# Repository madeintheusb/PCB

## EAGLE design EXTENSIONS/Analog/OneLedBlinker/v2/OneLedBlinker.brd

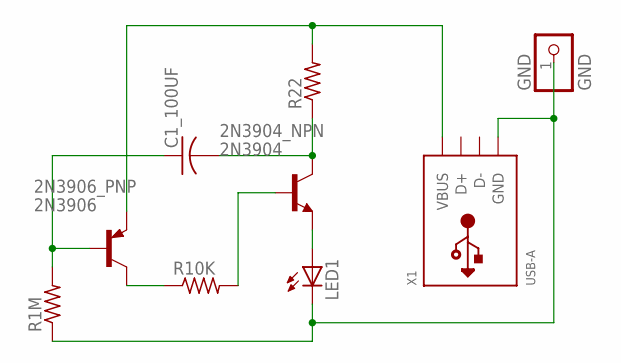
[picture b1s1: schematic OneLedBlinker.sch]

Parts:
2N3904_NPN: 2N3904; TO92
2N3906_PNP: 2N3906; TO92
C1_100UF: C-US025-030X050; C025-030X050
GND: GND; 1X01
LED1: LED5MM
R1M, R10K, R22: R-US_0207/10; 0207/10
X1: USB-A; MOLEX_480371000

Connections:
unnamed: 2N3906_PNP.3 (E), R22.2, X1.1 (VBUS)
unnamed: 2N3904_NPN.1 (C), C1_100UF.2, R22.1
unnamed: 2N3904_NPN.3 (E), LED1.A
unnamed: GND.1, LED1.K (C), R1M.1, X1.4 (GND)
unnamed: 2N3906_PNP.2 (B), C1_100UF.1, R1M.2
unnamed: 2N3906_PNP.1 (C), R10K.1
unnamed: 2N3904_NPN.2 (B), R10K.2

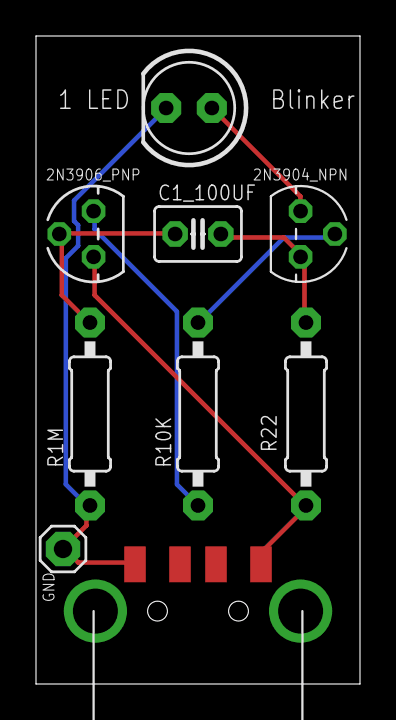
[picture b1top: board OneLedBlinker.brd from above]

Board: 2 copper layers, 18.0 x 36.0 mm, 9 parts (0 on the bottom side), 7 nets.

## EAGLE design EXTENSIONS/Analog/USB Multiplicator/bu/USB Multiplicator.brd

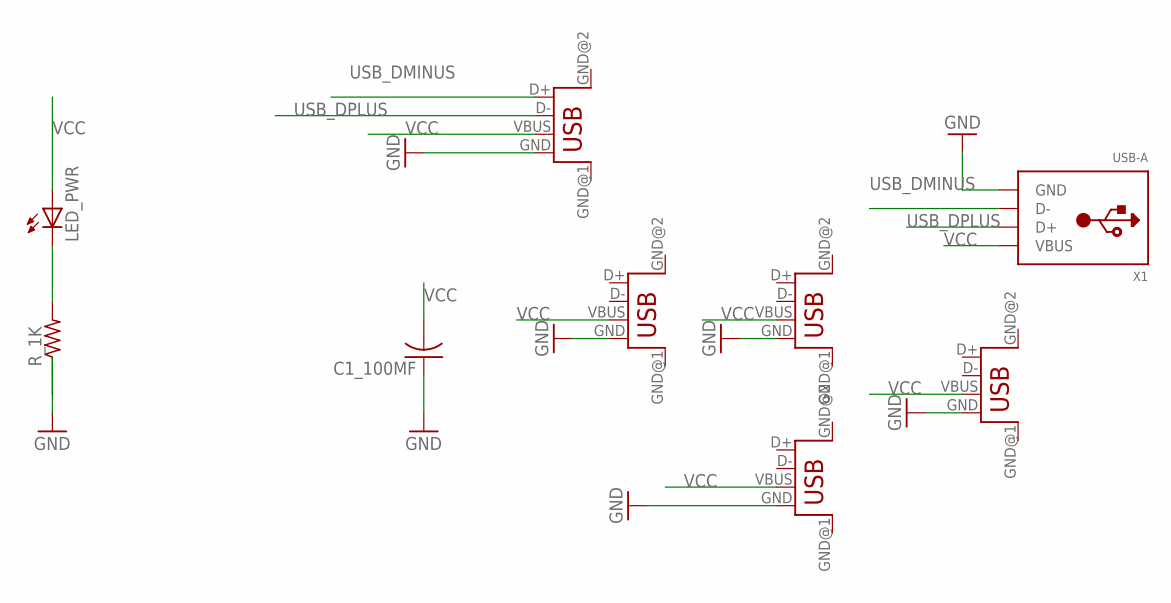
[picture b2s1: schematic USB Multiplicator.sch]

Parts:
C1_100MF: C-US025-030X050; C025-030X050
LED_PWR: LEDSMT1206; 1206
R_1K: R-US_R1206; R1206
USB_OUT_2, USB_OUT_3, USB_OUT_4, USB_OUT_5: USB; USB-FEMALE-A-PTH
USB_OUT_WITH_DATA_1: USB; USB-FEMALE-A-PTH
X1: USB-A; MOLEX_480371000

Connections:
GND: C1_100MF.1, R_1K.1, USB_OUT_2.GND, USB_OUT_3.GND, USB_OUT_4.GND, USB_OUT_5.GND, USB_OUT_WITH_DATA_1.GND, X1.4 (GND); also elsewhere on the board
unnamed: LED_PWR.C, R_1K.2
USB_DMINUS: USB_OUT_WITH_DATA_1.D+, X1.2 (D-)
USB_DPLUS: USB_OUT_WITH_DATA_1.D-, X1.3 (D+)
VCC: C1_100MF.2, LED_PWR.A, USB_OUT_2.VBUS, USB_OUT_3.VBUS, USB_OUT_4.VBUS, USB_OUT_5.VBUS, USB_OUT_WITH_DATA_1.VBUS, X1.1 (VBUS); also elsewhere on the board

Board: 2 copper layers, 10 parts (0 on the bottom side), 5 nets, no tracks yet.

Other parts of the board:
USB_OUT_6: USB; USB-FEMALE-A-PTH

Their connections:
GND: USB_OUT_6.GND; also elsewhere on the board
VCC: USB_OUT_6.VBUS; also elsewhere on the board

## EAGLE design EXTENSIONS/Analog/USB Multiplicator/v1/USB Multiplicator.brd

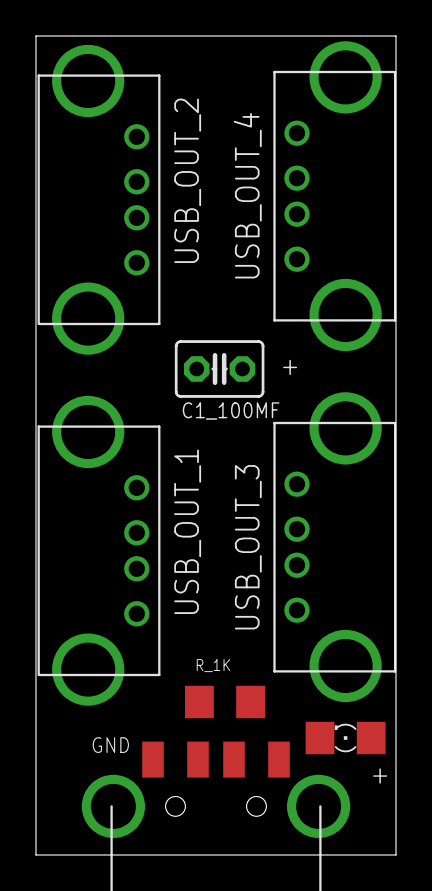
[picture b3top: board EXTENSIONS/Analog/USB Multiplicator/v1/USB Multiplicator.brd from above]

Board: 2 copper layers, 20.0 x 45.5 mm, 8 parts (0 on the bottom side), 5 nets, no tracks yet.

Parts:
C1_100MF: C025-030X050
LED_PWR: 1206
R_1K: R1206
USB_OUT_1, USB_OUT_2, USB_OUT_3, USB_OUT_4: USB; USB-FEMALE-A-PTH
X1: USB-A; MOLEX_480371000

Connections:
GND: C1_100MF.1, R_1K.1, USB_OUT_1.GND, USB_OUT_2.GND, USB_OUT_3.GND, USB_OUT_4.GND, X1.4
unnamed: LED_PWR.C, R_1K.2
USB_DMINUS: USB_OUT_1.D+, X1.2
USB_DPLUS: USB_OUT_1.D-, X1.3
VCC: C1_100MF.2, LED_PWR.A, USB_OUT_1.VBUS, USB_OUT_2.VBUS, USB_OUT_3.VBUS, USB_OUT_4.VBUS, X1.1

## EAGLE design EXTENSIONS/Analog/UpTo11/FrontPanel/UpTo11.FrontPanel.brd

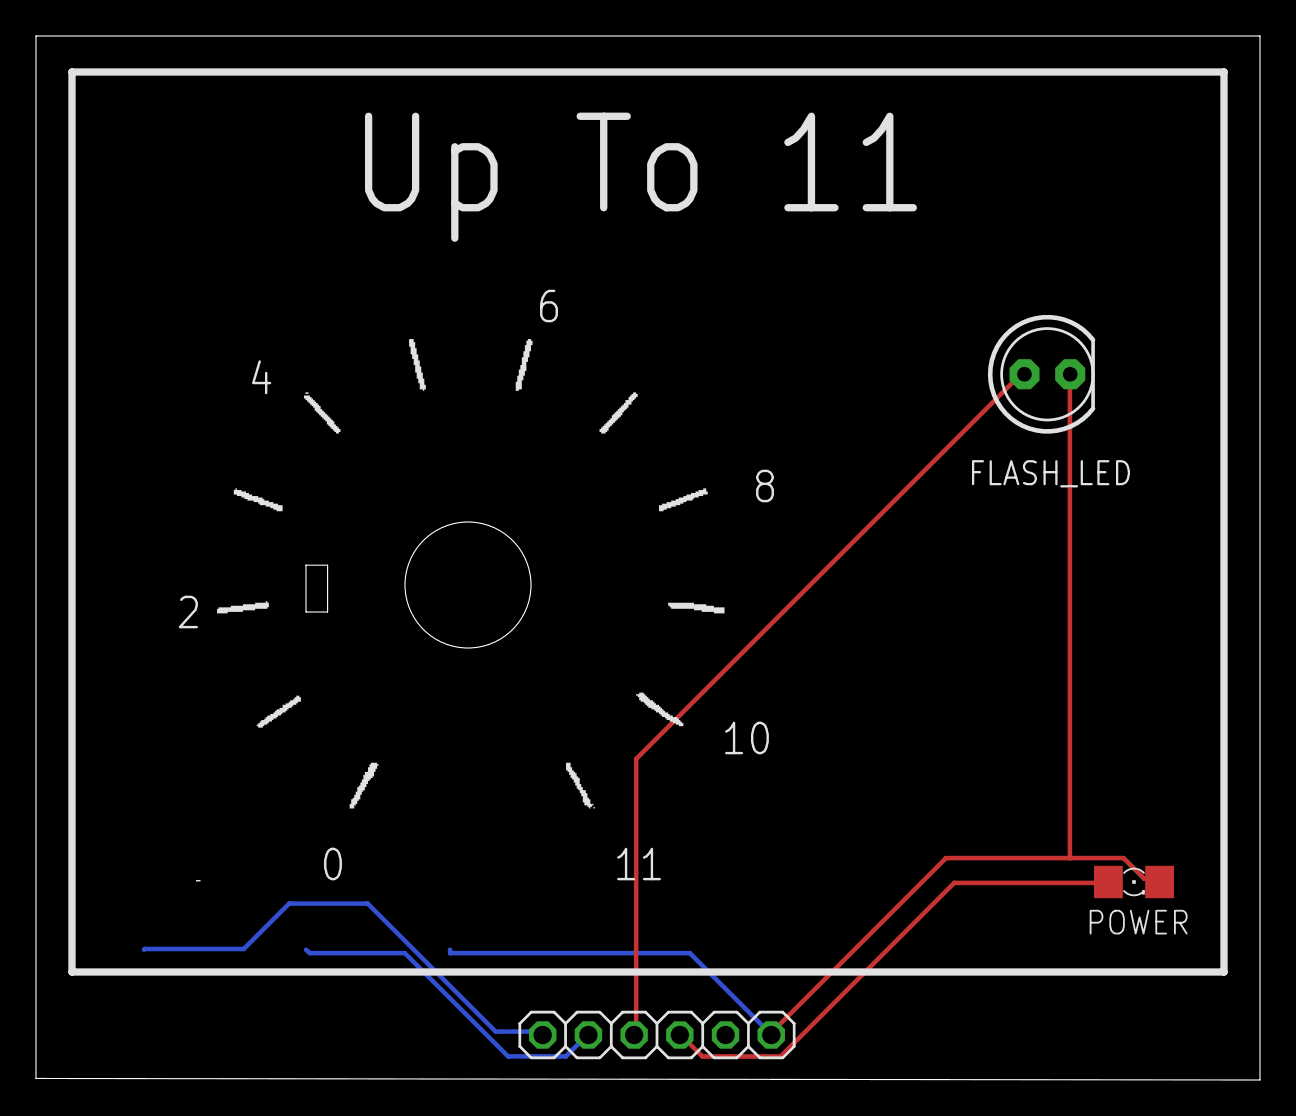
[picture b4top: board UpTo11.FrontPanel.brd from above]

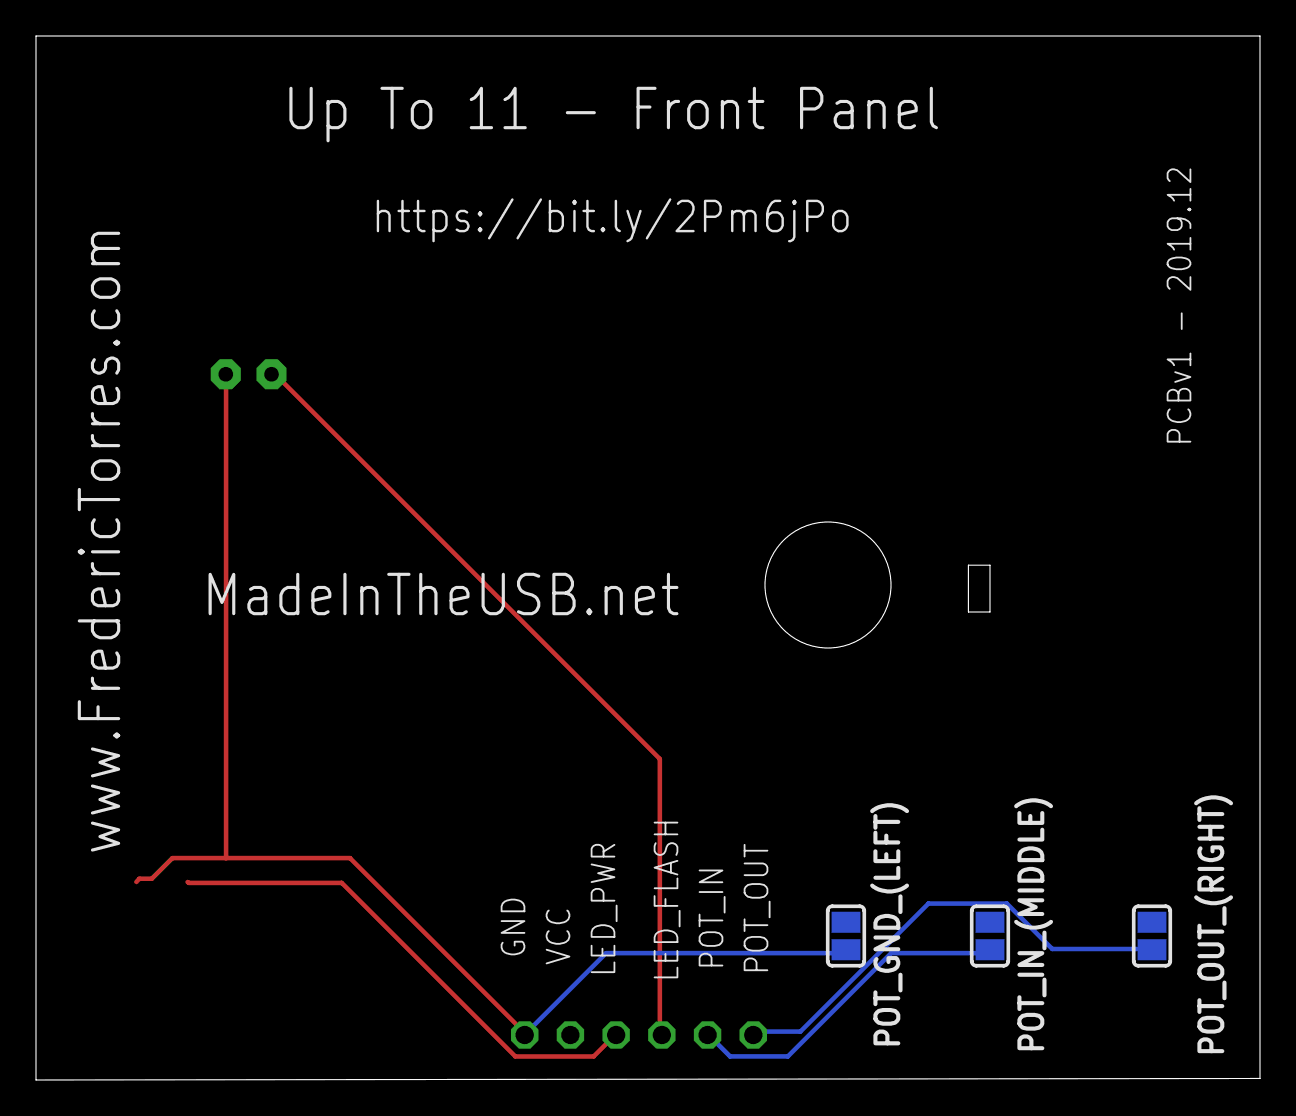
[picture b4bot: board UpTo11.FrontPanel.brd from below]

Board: 2 copper layers, 68.0 x 58.0 mm, 6 parts (3 on the bottom side), 5 nets.

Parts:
FLASH_LED: LED5MM
FRONT_PANEL_INTERFACE: 1X06
POT_GND_(LEFT): SOLDERJUMPER_REFLOW
POT_IN_(MIDDLE): SOLDERJUMPER_REFLOW
POT_OUT_(RIGHT): SOLDERJUMPER_REFLOW
POWER: 1206

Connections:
GND_EX: FLASH_LED.K, FRONT_PANEL_INTERFACE.1, POT_GND_(LEFT).2, POWER.C
LED_FLASH: FLASH_LED.A, FRONT_PANEL_INTERFACE.4
LED_PWR: FRONT_PANEL_INTERFACE.3, POWER.A
POT_IN: FRONT_PANEL_INTERFACE.5, POT_IN_(MIDDLE).2
POT_OUT: FRONT_PANEL_INTERFACE.6, POT_OUT_(RIGHT).2

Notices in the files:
parts and their libraries:
microbuilder: This work is placed in the public domain, and may be freely used for commercial and non-commercial work with the following conditions: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
